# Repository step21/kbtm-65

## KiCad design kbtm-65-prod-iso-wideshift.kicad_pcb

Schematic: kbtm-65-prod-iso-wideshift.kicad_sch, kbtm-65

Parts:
C1, C2: 22pF; C_0805_2012Metric
C3: 1uF; C_0805_2012Metric
C4, C5, C6, C8: 0.1uF; C_0805_2012Metric
C7: 10uF; C_0805_2012Metric
D0, D1, D2, D3, D4, D5, D6, D7, D8, D9, D10, D11, D12, D13, D14, D15, D16, D17, D18, D19, D20, D21, D22, D23, D24, D25, D26, D27, D28, D29, D30, D31, D32, D33, D34, D35, D36, D37, D38, D39, D40, D41, D42, D43, D44, D45, D46, D47, D48, D49, D50, D51, D52, D53, D54, D55, D56, D57, D58, D59, D60, D61, D62, D63, D64, D65, D66, D67, D68: 1N4148W; D_SOD123_axial-dual
F1: 500mA; Fuse_1206_3216Metric
H0, H1, H2, H3, H4, H5: Mounting Hole; MountingHole_2.2mm_M2_Pad_tweaked
J1: TYPE-C-31-M12_13_EDITED; HRO-TYPE-C-31-M-12-HandSoldering_tweaked
J2: AVR-ISP-6; ICSP_2.54mm_LAYOUT
LO0: kbtm65-SilkScreen; eLiXiVy-rev1.1-SilkScreen
LO1: kbtm65-Mask; eLiXiVy-rev1.1-Mask
LO2: OSHW-Logo
MX_0, MX_1, MX_2, MX_3, MX_4, MX_5, MX_6, MX_7, MX_8, MX_9, MX_.1: MX-NoLED; MXOnly-1U-NoLED_tweak
MX_1.5U_TAB1, MX_1.5U_\1: MX-NoLED; MXOnly-1.5U-NoLED_tweak
MX_1.25U_FN1, MX_1.25U_L_ALT1, MX_1.25U_L_CTRL1, MX_1.25U_L_SHIFT1, MX_1.25U_L_WIN1, MX_1.25U_R_CTRL1: MX-NoLED; MXOnly-1.25U-NoLED_tweak
MX_1.75U_CAPSLOCK1, MX_1.75U__RSHIFT1: MX-NoLED; MXOnly-1.75U-NoLED_tweak
MX_2.25U_ENTER1, MX_2.25U_LSHIFT1: MX-NoLED; MXOnly-2.25U-NoLED_tweak
MX_2U_BACKSP1: MX-NoLED; MXOnly-2U-NoLED_tweak
MX_6.25U_SPACE1: MX-NoLED; MXOnly-6.25U-ReversedStabilizers-NoLED_tweak
MX_'1: MX-NoLED; MXOnly-1U-NoLED_tweak
MX_,1: MX-NoLED; MXOnly-1U-NoLED_tweak
MX_/1: MX-NoLED; MXOnly-1U-NoLED_tweak
MX_;1: MX-NoLED; MXOnly-1U-NoLED_tweak
MX_A1: MX-NoLED; MXOnly-1U-NoLED_tweak
MX_ARR_D1: MX-NoLED; MXOnly-1U-NoLED_tweak
MX_ARR_L1: MX-NoLED; MXOnly-1U-NoLED_tweak
MX_ARR_R1: MX-NoLED; MXOnly-1U-NoLED_tweak
MX_ARR_U1: MX-NoLED; MXOnly-1U-NoLED_tweak
MX_B1: MX-NoLED; MXOnly-1U-NoLED_tweak
MX_C1: MX-NoLED; MXOnly-1U-NoLED_tweak
MX_D1: MX-NoLED; MXOnly-1U-NoLED_tweak
MX_DASH1: MX-NoLED; SW_Hotswap_Kailh_MX_Plated_1.00u
MX_DEL1: MX-NoLED; MXOnly-1U-NoLED_tweak
MX_E1: MX-NoLED; MXOnly-1U-NoLED_tweak
MX_ESC1: MX-NoLED; MXOnly-1U-NoLED_tweak
MX_F1: MX-NoLED; MXOnly-1U-NoLED_tweak
MX_FN1: MX-NoLED; MXOnly-1U-NoLED_tweak
MX_G1: MX-NoLED; MXOnly-1U-NoLED_tweak
MX_H1: MX-NoLED; MXOnly-1U-NoLED_tweak
MX_I1: MX-NoLED; MXOnly-1U-NoLED_tweak
MX_INS1: MX-NoLED; MXOnly-1U-NoLED_tweak
MX_ISO_ENTER1: MX-NoLED; MXOnly-ISO-ROTATED-ReversedStabilizers-NoLED_tweak
MX_ISO_\1: MX-NoLED; MXOnly-1U-NoLED_tweak
MX_J1: MX-NoLED; MXOnly-1U-NoLED_tweak
MX_K1: MX-NoLED; MXOnly-1U-NoLED_tweak
MX_KAILH_SOCKET_EQUALS1: MX-NoLED; SW_Hotswap_Kailh_MX_Plated_1.00u
MX_L1: MX-NoLED; MXOnly-1U-NoLED_tweak
MX_L_ALT1: MX-NoLED; MXOnly-1U-NoLED_tweak
MX_L_BSLASH1: MX-NoLED; MXOnly-1U-NoLED_tweak
MX_M1: MX-NoLED; MXOnly-1U-NoLED_tweak
MX_N1: MX-NoLED; MXOnly-1U-NoLED_tweak
MX_O1: MX-NoLED; MXOnly-1U-NoLED_tweak
MX_P1: MX-NoLED; MXOnly-1U-NoLED_tweak
MX_PrtSc1: MX-NoLED; MXOnly-1U-NoLED_tweak
MX_Q1: MX-NoLED; MXOnly-1U-NoLED_tweak
MX_R1: MX-NoLED; MXOnly-1U-NoLED_tweak
MX_R_CTRL1: MX-NoLED; MXOnly-1U-NoLED_tweak
MX_S1: MX-NoLED; MXOnly-1U-NoLED_tweak
MX_STEP_CAPS1: MX-NoLED; MXOnly-1U-NoLED_tweak
MX_T1: MX-NoLED; MXOnly-1U-NoLED_tweak
MX_TEMP1: MX-NoLED; MXOnly-1U-NoLED_tweak
MX_U1: MX-NoLED; MXOnly-1U-NoLED_tweak
MX_V1: MX-NoLED; MXOnly-1U-NoLED_tweak
MX_W1: MX-NoLED; MXOnly-1U-NoLED_tweak
MX_X1: MX-NoLED; MXOnly-1U-NoLED_tweak
MX_Y1: MX-NoLED; MXOnly-1U-NoLED_tweak
MX_Z1: MX-NoLED; MXOnly-1U-NoLED_tweak
MX_[1: MX-NoLED; MXOnly-1U-NoLED_tweak
MX_]1: MX-NoLED; MXOnly-1U-NoLED_tweak
R1, R4: 10k; R_0805_2012Metric
R2, R3: 22; R_0805_2012Metric
R5, R6: 5.1k; R_0805_2012Metric
RE0: Rotary_Encoder_Switch; RotaryEncoder_Alps_EC11E-Switch-Vertical-EDIT
SW1: SW_Push; SKQG-1155865
SW2: RotaryEncoder_Switch; RotaryEncoder_Alps_EC11E-Switch_Vertical_H20mm; LCSC C470753
SW3: SW_Push; SW_Hotswap_Kailh_MX_plated_1.00u; LCSC C2803348
U1: ATmega32U4-AU; TQFP-44_10x10mm_P0.8mm_ATmega32U4
U2: WE-TVS-82400102; SOT-23-6_tweaked
Y1: Crystal_GND24_Small; Crystal_SMD_3225-4Pin_3.2x2.5mm

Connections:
+5V: C4.1, C5.1, C6.1, C7.1, C8.1, F1.1, J2.2 (VCC), R1.1, U1.2, U1.7, U1.14, U1.24, U1.34, U1.44, U2.5
COL0: MX_1.5U_TAB1.1 (COL), MX_1.25U_L_CTRL1.1 (COL), MX_1.25U_L_SHIFT1.1 (COL), MX_1.75U_CAPSLOCK1.1 (COL), MX_2.25U_LSHIFT1.1 (COL), MX_ESC1.1 (COL), MX_STEP_CAPS1.1 (COL), U1.36
COL1: MX_1.1 (COL), MX_1.25U_L_WIN1.1 (COL), MX_A1.1 (COL), MX_L_BSLASH1.1 (COL), MX_Q1.1 (COL), U1.38
COL2: MX_1.25U_L_ALT1.1 (COL), MX_2.1 (COL), MX_S1.1 (COL), MX_W1.1 (COL), MX_Z1.1 (COL), U1.39
COL3: MX_3.1 (COL), MX_D1.1 (COL), MX_E1.1 (COL), MX_X1.1 (COL), U1.40
COL4: MX_4.1 (COL), MX_C1.1 (COL), MX_F1.1 (COL), MX_R1.1 (COL), U1.41
COL5: MX_5.1 (COL), MX_G1.1 (COL), MX_T1.1 (COL), MX_V1.1 (COL), U1.12
COL6: MX_6.1 (COL), MX_6.25U_SPACE1.1 (COL), MX_B1.1 (COL), MX_H1.1 (COL), MX_Y1.1 (COL), U1.18
COL7: MX_7.1 (COL), MX_J1.1 (COL), MX_N1.1 (COL), MX_U1.1 (COL), U1.19
COL8: MX_8.1 (COL), MX_I1.1 (COL), MX_K1.1 (COL), MX_M1.1 (COL), U1.20
COL9: MX_1.25U_R_CTRL1.1 (COL), MX_9.1 (COL), MX_,1.1 (COL), MX_L1.1 (COL), MX_L_ALT1.1 (COL), MX_O1.1 (COL), U1.21
COL10: MX_0.1 (COL), MX_1.25U_FN1.1 (COL), MX_.1.1 (COL), MX_;1.1 (COL), MX_FN1.1 (COL), MX_P1.1 (COL), U1.25
COL11: MX_'1.1 (COL), MX_/1.1 (COL), MX_DASH1.1 (COL), MX_R_CTRL1.1 (COL), MX_[1.1 (COL), U1.26
COL12: MX_1.75U__RSHIFT1.1 (COL), MX_2.25U_ENTER1.1 (COL), MX_ARR_L1.1 (COL), MX_ISO_\1.1 (COL), MX_KAILH_SOCKET_EQUALS1.1 (COL), MX_]1.1 (COL), U1.27; also elsewhere on the board
COL13: MX_1.5U_\1.1 (COL), MX_2U_BACKSP1.1 (COL), MX_ARR_D1.1 (COL), MX_ARR_U1.1 (COL), MX_ISO_ENTER1.1 (COL), U1.28
COL14: MX_ARR_R1.1 (COL), MX_DEL1.1 (COL), MX_INS1.1 (COL), MX_PrtSc1.1 (COL), MX_TEMP1.1 (COL), RE0.S2, U1.31
D+: R2.1, U1.4
D-: R3.1, U1.3
GND: C1.2, C2.2, C3.2, C4.2, C5.2, C6.2, C7.2, C8.2, H0.1, J1.1 (GND), J1.12 (GND), J1.13 (SHIELD), J2.6 (GND), R4.1, R5.1, R6.1, RE0.C, SW1.1, U1.5, U1.15, U1.23, U1.35, U1.43, U2.2, Y1.2, Y1.4
MCU_D+: R2.2, U2.4
MCU_D-: R3.2, U2.6
MISO: J2.1 (MISO), U1.11
MOSI: J2.4 (MOSI), U1.10
unnamed: C3.1, U1.6
unnamed: D0.2 (A), MX_ESC1.2 (ROW)
unnamed: D1.2 (A), MX_1.2 (ROW)
unnamed: D2.2 (A), MX_2.2 (ROW)
unnamed: D3.2 (A), MX_3.2 (ROW)
unnamed: D4.2 (A), MX_4.2 (ROW)
unnamed: D5.2 (A), MX_5.2 (ROW)
unnamed: D6.2 (A), MX_6.2 (ROW)
unnamed: D7.2 (A), MX_7.2 (ROW)
unnamed: D8.2 (A), MX_8.2 (ROW)
unnamed: D9.2 (A), MX_9.2 (ROW)
unnamed: D10.2 (A), MX_0.2 (ROW)
unnamed: D11.2 (A), MX_DASH1.2 (ROW)
unnamed 36: D12.2 (A), MX_KAILH_SOCKET_EQUALS1.2 (ROW); also elsewhere on the board
unnamed: D13.2 (A), MX_2U_BACKSP1.2 (ROW)
unnamed: D15.2 (A), MX_1.5U_TAB1.2 (ROW)
unnamed: D16.2 (A), MX_Q1.2 (ROW)
unnamed: D17.2 (A), MX_W1.2 (ROW)
unnamed: D18.2 (A), MX_E1.2 (ROW)
unnamed: D19.2 (A), MX_R1.2 (ROW)
unnamed: D20.2 (A), MX_T1.2 (ROW)
unnamed: D21.2 (A), MX_Y1.2 (ROW)
unnamed: D22.2 (A), MX_U1.2 (ROW)
unnamed: D23.2 (A), MX_I1.2 (ROW)
unnamed: D24.2 (A), MX_O1.2 (ROW)
unnamed: D25.2 (A), MX_P1.2 (ROW)
unnamed: D26.2 (A), MX_[1.2 (ROW)
unnamed: D27.2 (A), MX_]1.2 (ROW)
unnamed: D28.2 (A), MX_1.5U_\1.2 (ROW), MX_ISO_ENTER1.2 (ROW)
unnamed: D29.2 (A), MX_DEL1.2 (ROW)
unnamed: D30.2 (A), MX_1.75U_CAPSLOCK1.2 (ROW), MX_STEP_CAPS1.2 (ROW)
unnamed: D31.2 (A), MX_A1.2 (ROW)
unnamed: D32.2 (A), MX_S1.2 (ROW)
unnamed: D33.2 (A), MX_D1.2 (ROW)
unnamed: D34.2 (A), MX_F1.2 (ROW)
unnamed: D35.2 (A), MX_G1.2 (ROW)
unnamed: D36.2 (A), MX_H1.2 (ROW)
unnamed: D37.2 (A), MX_J1.2 (ROW)
unnamed: D38.2 (A), MX_K1.2 (ROW)
unnamed: D39.2 (A), MX_L1.2 (ROW)
unnamed: D40.2 (A), MX_;1.2 (ROW)
unnamed: D41.2 (A), MX_'1.2 (ROW)
unnamed: D42.2 (A), MX_2.25U_ENTER1.2 (ROW), MX_ISO_\1.2 (ROW)
unnamed: D43.2 (A), MX_INS1.2 (ROW)
unnamed: D44.2 (A), MX_1.25U_L_SHIFT1.2 (ROW), MX_2.25U_LSHIFT1.2 (ROW)
unnamed: D45.2 (A), MX_L_BSLASH1.2 (ROW)
unnamed: D46.2 (A), MX_Z1.2 (ROW)
unnamed: D47.2 (A), MX_X1.2 (ROW)
unnamed: D48.2 (A), MX_C1.2 (ROW)
unnamed: D49.2 (A), MX_V1.2 (ROW)
unnamed: D50.2 (A), MX_B1.2 (ROW)
unnamed: D51.2 (A), MX_N1.2 (ROW)
unnamed: D52.2 (A), MX_M1.2 (ROW)
unnamed: D53.2 (A), MX_,1.2 (ROW)
unnamed: D54.2 (A), MX_.1.2 (ROW)
unnamed: D55.2 (A), MX_/1.2 (ROW)
unnamed: D56.2 (A), MX_1.75U__RSHIFT1.2 (ROW)
unnamed: D57.2 (A), MX_ARR_U1.2 (ROW)
unnamed: D58.2 (A), MX_TEMP1.2 (ROW)
unnamed: D59.2 (A), MX_1.25U_L_CTRL1.2 (ROW)
unnamed: D60.2 (A), MX_1.25U_L_WIN1.2 (ROW)
unnamed: D61.2 (A), MX_1.25U_L_ALT1.2 (ROW)
unnamed: D62.2 (A), MX_6.25U_SPACE1.2 (ROW)
unnamed: D63.2 (A), MX_1.25U_R_CTRL1.2 (ROW), MX_L_ALT1.2 (ROW)
unnamed: D64.2 (A), MX_1.25U_FN1.2 (ROW), MX_FN1.2 (ROW)
unnamed: D65.2 (A), MX_R_CTRL1.2 (ROW)
unnamed: D66.2 (A), MX_ARR_L1.2 (ROW)
unnamed: D67.2 (A), MX_ARR_D1.2 (ROW)
unnamed: D68.2 (A), MX_ARR_R1.2 (ROW)
unnamed: J1.4 (CC1), R5.2
unnamed: J1.10 (CC2), R6.2
unnamed: R4.2, U1.33
RE+: RE0.B, U1.22
RE-: RE0.A, U1.8
RESET: J2.5 (~RST), R1.2, SW1.2, U1.13
ROW0: D0.1 (K), D1.1 (K), D2.1 (K), D3.1 (K), D4.1 (K), D5.1 (K), D6.1 (K), D7.1 (K), D8.1 (K), D9.1 (K), D10.1 (K), D11.1 (K), D12.1 (K), D13.1 (K), D14.1 (K), U1.29
ROW0_RE: D14.2 (A), MX_PrtSc1.2 (ROW), RE0.S1
ROW1: D15.1 (K), D16.1 (K), D17.1 (K), D18.1 (K), D19.1 (K), D20.1 (K), D21.1 (K), D22.1 (K), D23.1 (K), D24.1 (K), D25.1 (K), D26.1 (K), D27.1 (K), D28.1 (K), D29.1 (K), U1.30
ROW2: D30.1 (K), D31.1 (K), D32.1 (K), D33.1 (K), D34.1 (K), D35.1 (K), D36.1 (K), D37.1 (K), D38.1 (K), D39.1 (K), D40.1 (K), D41.1 (K), D42.1 (K), D43.1 (K), U1.1
ROW3: D44.1 (K), D45.1 (K), D46.1 (K), D47.1 (K), D48.1 (K), D49.1 (K), D50.1 (K), D51.1 (K), D52.1 (K), D53.1 (K), D54.1 (K), D55.1 (K), D56.1 (K), D57.1 (K), D58.1 (K), U1.37
ROW4: D59.1 (K), D60.1 (K), D61.1 (K), D62.1 (K), D63.1 (K), D64.1 (K), D65.1 (K), D66.1 (K), D67.1 (K), D68.1 (K), U1.32
SCK: J2.3 (SCK), U1.9
USB_D+: J1.6 (D+), J1.8 (D+), U2.3
USB_D-: J1.5 (D-), J1.7 (D-), U2.1
VCC: F1.2, J1.2 (VBUS), J1.11 (VBUS)
XTAL1: C1.1, U1.17, Y1.1
XTAL2: C2.1, U1.16, Y1.3

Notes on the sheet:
Crystal
Mechanical Keyswitch Matrix
Decoupling Capacitors
Electrical Protection
Rotary Encoder
kbtm-65 Schematic, Rev 1.3
github.com/minibois/eLiXiVy
ICSP Header
ESD TVS Diode
2021
Logos
Mounting Holes
Microcontroller (atmega32u4)
rev.1.1
USB Type C
Polyfuse

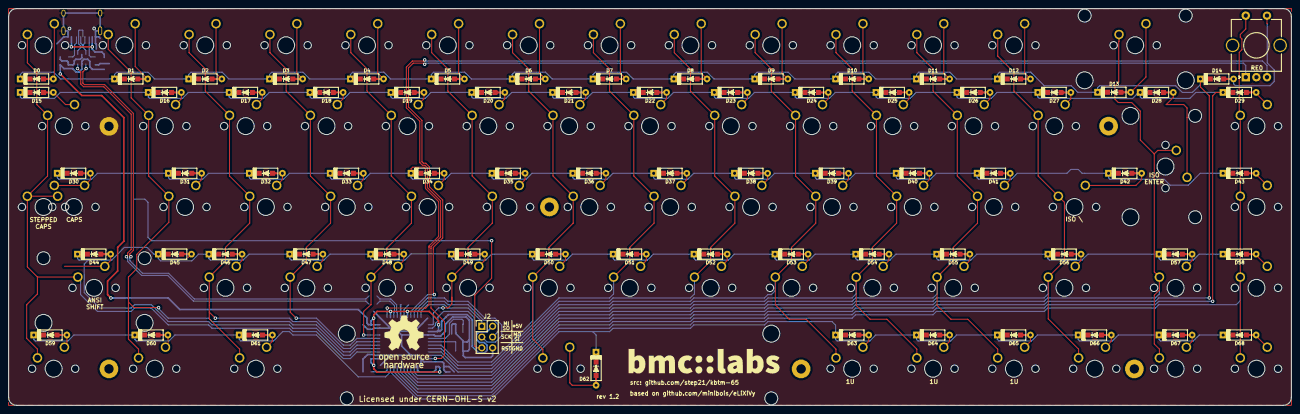
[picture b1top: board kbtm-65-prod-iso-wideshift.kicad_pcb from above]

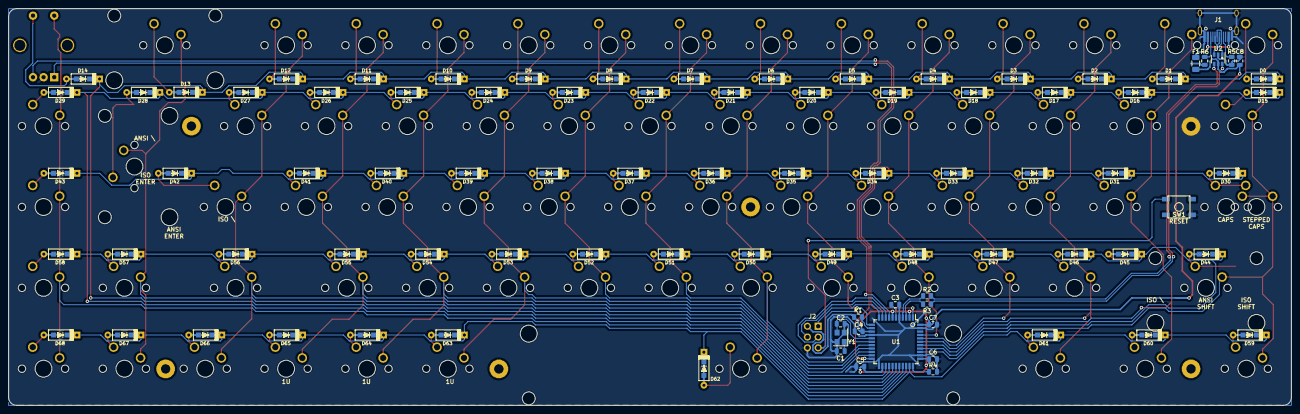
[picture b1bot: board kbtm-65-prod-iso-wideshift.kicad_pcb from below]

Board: 2 copper layers, 302.2 x 93.5 mm, 167 parts (20 on the bottom side), 109 nets.

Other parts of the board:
MX_EQUALS1: MX-NoLED; MXOnly-1U-NoLED_tweak

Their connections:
COL12: MX_EQUALS1.1; also elsewhere on the board
unnamed 36: MX_EQUALS1.2; also elsewhere on the board

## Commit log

2023-11-18 modified repo text and branding etc
2023-11-19 updated cache and added logo footprint
2023-11-19 placed bmc labs logo
2023-11-19 added bmc labs logo to bmc-labs library
2023-11-19 added gerber files for rev 1.2
2023-11-21 added bmclabs logo
2023-11-21 added pcb files for prod of iso wideshift etc
2023-11-21 added prl file for original file
2023-11-21 final prod version with all keys and fills filled in
2023-11-29 replaced soldered switches with kailh mx sockets

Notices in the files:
kbtm-65-prod-iso-wideshift.kicad_pcb:
Full License: https://github.com/minibois/eLiXiVy/blob/master/LICENSE.txt
This PCB file describes Open Hardware and is licensed under the CERN-OHL-S v2.
kbtm-65 Copyright BMC-Labs 2023.
Licensed under CERN-OHL-S v2
kbtm-65-prod-iso-wideshift.kicad_sch:
This schematic describes Open Hardware and is licensed under the CERN-OHL-S v2.
